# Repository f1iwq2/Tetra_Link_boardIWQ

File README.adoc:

Tetra_Link_boardIWQ
===================
 
Tetra board for the Pi Svxlink-tetra
Kicad Electronic Schematics & documentation
 
Carte Tetra pour le Pi
Schémas Kicad & documentation
 
image::interface_MTM800E_V4.jpg[]

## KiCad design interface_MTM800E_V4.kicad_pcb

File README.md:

# Tetra Link board
Tetra board for the Pi Svxlink-tetra
 Kicad Electronic Schematics & documentation
 
 (dir doc)
Carte Svxlink Tetra pour le Pi
 Schémas Kicad & documentation
 (rep doc)

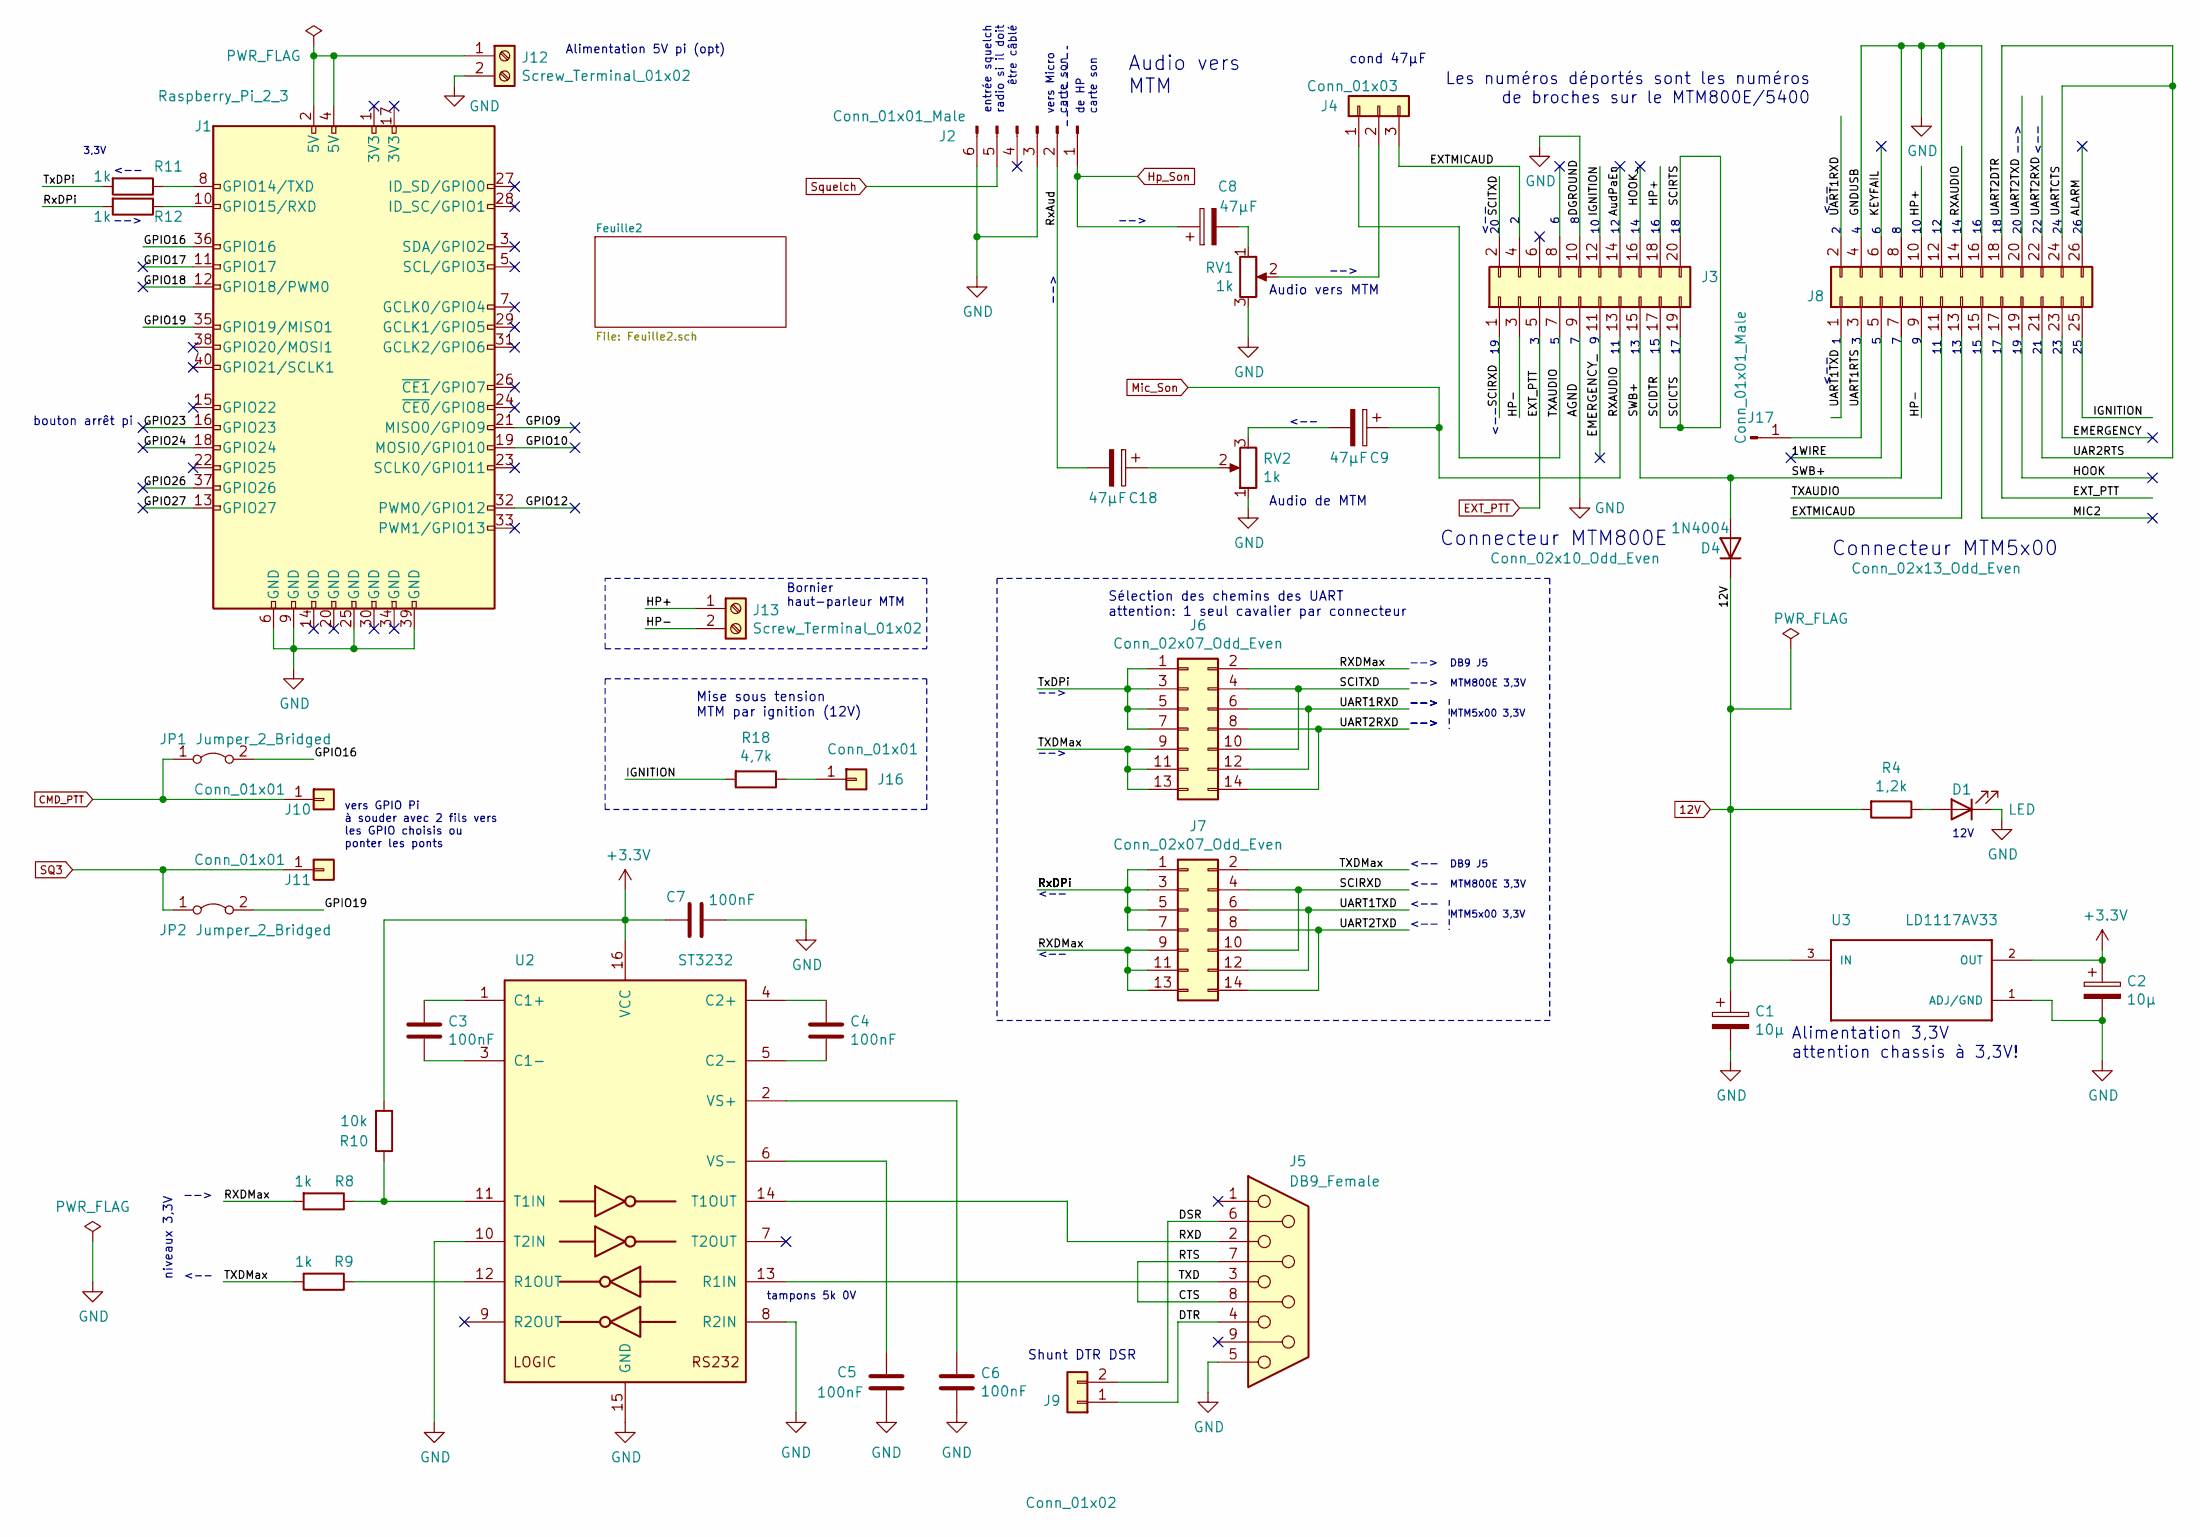
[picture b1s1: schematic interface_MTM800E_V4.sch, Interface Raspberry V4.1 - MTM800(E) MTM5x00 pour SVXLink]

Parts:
C1, C2: 10µ; CP_Radial_D5.0mm_P2.50mm
C3, C4, C5, C6, C7: 100nF; C_0805_2012Metric
C8, C9, C18: 47µF; CP_Radial_D4.0mm_P2.00mm
D1: LED; LED_D3.0mm
D4: 1N4004; D_A-405_P5.08mm_Vertical_AnodeUp
J1: Raspberry_Pi_2_3; raspberrypi2
J2: Conn_01x01_Male; PinHeader_1x06_P2.54mm_Vertical
J3: Conn_02x10_Odd_Even; PinHeader_2x10_P2.54mm_Vertical
J4: Conn_01x03; PinHeader_1x03_P2.54mm_Vertical
J5: DB9_Female; DSUB-9_Female_Horizontal_P2.77x2.84mm_EdgePinOffset9.90mm_H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
J6, J7: Conn_02x07_Odd_Even; PinHeader_2x07_P2.54mm_Vertical
J8: Conn_02x13_Odd_Even; PinHeader_2x13_P2.54mm_Vertical
J9: Conn_01x02; PinHeader_1x02_P2.54mm_Vertical
J10, J11: Conn_01x01; TestPoint_Loop_D2.50mm_Drill1.0mm
J12, J13: Screw_Terminal_01x02; TerminalBlock_bornier-2_P5.08mm
J16: Conn_01x01; PinHeader_1x01_P2.54mm_Vertical
J17: Conn_01x01_Male; PinHeader_1x01_P2.54mm_Vertical
JP1, JP2: Jumper_2_Bridged; SolderJumper-2_P1.3mm_Open_TrianglePad1.0x1.5mm
R4: 1,2k; R_Axial_DIN0207_L6.3mm_D2.5mm_P7.62mm_Horizontal
R8: 1k; R_Axial_DIN0207_L6.3mm_D2.5mm_P7.62mm_Horizontal
R9, R11, R12: 1k; R_Axial_DIN0204_L3.6mm_D1.6mm_P2.54mm_Vertical
R10: 10k; R_Axial_DIN0207_L6.3mm_D2.5mm_P7.62mm_Horizontal
R18: 4,7k; R_Axial_DIN0207_L6.3mm_D2.5mm_P7.62mm_Horizontal
RV1, RV2: 1k; Potentiometer_Bourns_3296W_Vertical
U2: ST3232; SOIC-16_3.9x9.9mm_P1.27mm
U3: LD1117AV33; TO255P1020X450X1968-3

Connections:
12V: C1.1, D4.1 (K), R4.2, U3.3 (IN); also elsewhere on the board
+3V3: C2.1, C7.1, R10.2, U2.16 (VCC), U3.2 (OUT); also elsewhere on the board
/1WIRE: J8.5
/ALARM: J8.26
/AudPaEn: J3.14
/CTS: J5.7, J5.8
/DSR: J5.6, J9.2
/DTR: J5.4, J9.1
/EMERGENCY: J8.23
/EMERGENCY_: J3.11
/EXTMICAUD: J3.4, J4.3, J8.13
/GPIO9: J1.21 (MISO0/GPIO9)
/GPIO10: J1.19 (MOSI0/GPIO10)
/GPIO12: J1.32 (PWM0/GPIO12)
/GPIO16: J1.36 (GPIO16), JP1.2 (B)
/GPIO17: J1.11 (GPIO17)
/GPIO18: J1.12 (GPIO18/PWM0)
/GPIO19: J1.35 (GPIO19/MISO1), JP2.2 (B)
/GPIO23: J1.16 (GPIO23)
/GPIO24: J1.18 (GPIO24)
/GPIO26: J1.37 (GPIO26)
/GPIO27: J1.13 (GPIO27)
/HOOK: J8.19
/HOOK_: J3.16
/HP+: J3.18, J8.10, J13.1
/HP-: J3.3, J8.9, J13.2
/IGNITION: J3.12, J8.25, R18.2
/KEYFAIL: J8.6
/MIC2: J8.15
/RXD: J5.2, U2.14 (T1OUT)
/RXDMax: J6.2, J7.9, J7.11, J7.13, R8.2
/RxDPi: J7.1, J7.3, J7.5, J7.7, R12.2
/SCICTS: J3.17, J3.19, J3.20
/SCIRXD: J3.1, J7.4, J7.10
/SCITXD: J3.2, J6.4, J6.10
/SWB+: D4.2 (A), J3.15, J8.7
/TXAUDIO: J3.7, J4.1, J8.11
/TXD: J5.3, U2.13 (R1IN)
/TXDMax: J6.9, J6.11, J6.13, J7.2, R9.2
/TxDPi: J6.1, J6.3, J6.5, J6.7, R11.2
/UAR2RTS: J8.18, J8.21, J8.24
/UART1RTS: J8.3, J17.1
/UART1RXD: J6.6, J6.12, J8.2
/UART1TXD: J7.6, J7.12, J8.1
/UART2RXD: J6.8, J6.14, J8.22
/UART2TXD: J7.8, J7.14, J8.20
CMD_PTT: J10.1, JP1.1 (A); also elsewhere on the board
EXT_PTT: J3.5, J8.17; also elsewhere on the board
GND: C1.2, C2.2, C5.2, C6.2, C7.2, D1.1 (K), J1.6 (GND), J1.9 (GND), J1.25 (GND), J1.39 (GND), J2.3, J2.6, J3.9, J3.10, J5.5, J8.4, J8.8, J8.12, J8.16, J12.2, RV1.3, RV2.1, U2.8 (R2IN), U2.10 (T2IN), U2.15 (GND), U3.1 (ADJ/GND); also elsewhere on the board
Mic_Son: C9.1, J3.13, J8.14; also elsewhere on the board
unnamed: C3.1, U2.1 (C1+)
unnamed: C3.2, U2.3 (C1-)
unnamed: C4.1, U2.4 (C2+)
unnamed: C4.2, U2.5 (C2-)
unnamed: C5.1, U2.6 (VS-)
unnamed: C6.1, U2.2 (VS+)
unnamed: C9.2, RV2.3
unnamed: D1.2 (A), R4.1
unnamed: J1.2 (5V), J1.4 (5V), J12.1
unnamed: J1.8 (GPIO14/TXD), R11.1
unnamed: J1.10 (GPIO15/RXD), R12.1
unnamed: J4.2, RV1.2
unnamed: J16.1, R18.1
unnamed: R9.1, U2.12 (R1OUT)
unnamed: R8.1, R10.1, U2.11 (T1IN)
SQ3: J11.1, JP2.1 (A); also elsewhere on the board
Squelch: J2.5; also elsewhere on the board

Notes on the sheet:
Connecteur MTM800E
Les numéros déportés sont les numéros de broches sur le MTM800E/5400
Audio vers MTM
Audio de MTM
niveaux 3,3V
Alimentation 3,3V attention chassis à 3,3V!
Connecteur MTM5x00
Shunt DTR DSR
vers GPIO Pi à souder avec 2 fils vers les GPIO choisis ou ponter les ponts
Alimentation 5V pi (opt)
vers Micro carte son
de HP carte son
12V
Bornier haut-parleur MTM
<--
-->
tampons 5k 0V
bouton arrêt pi
Mise sous tension MTM par ignition (12V)
Sélection des chemins des UART attention: 1 seul cavalier par connecteur
Audio vers MTM
entrée squelch radio si il doit être câblé
MTM800E 3,3V
MTM5x00 3,3V
3,3V
DB9 J5
cond 47µF

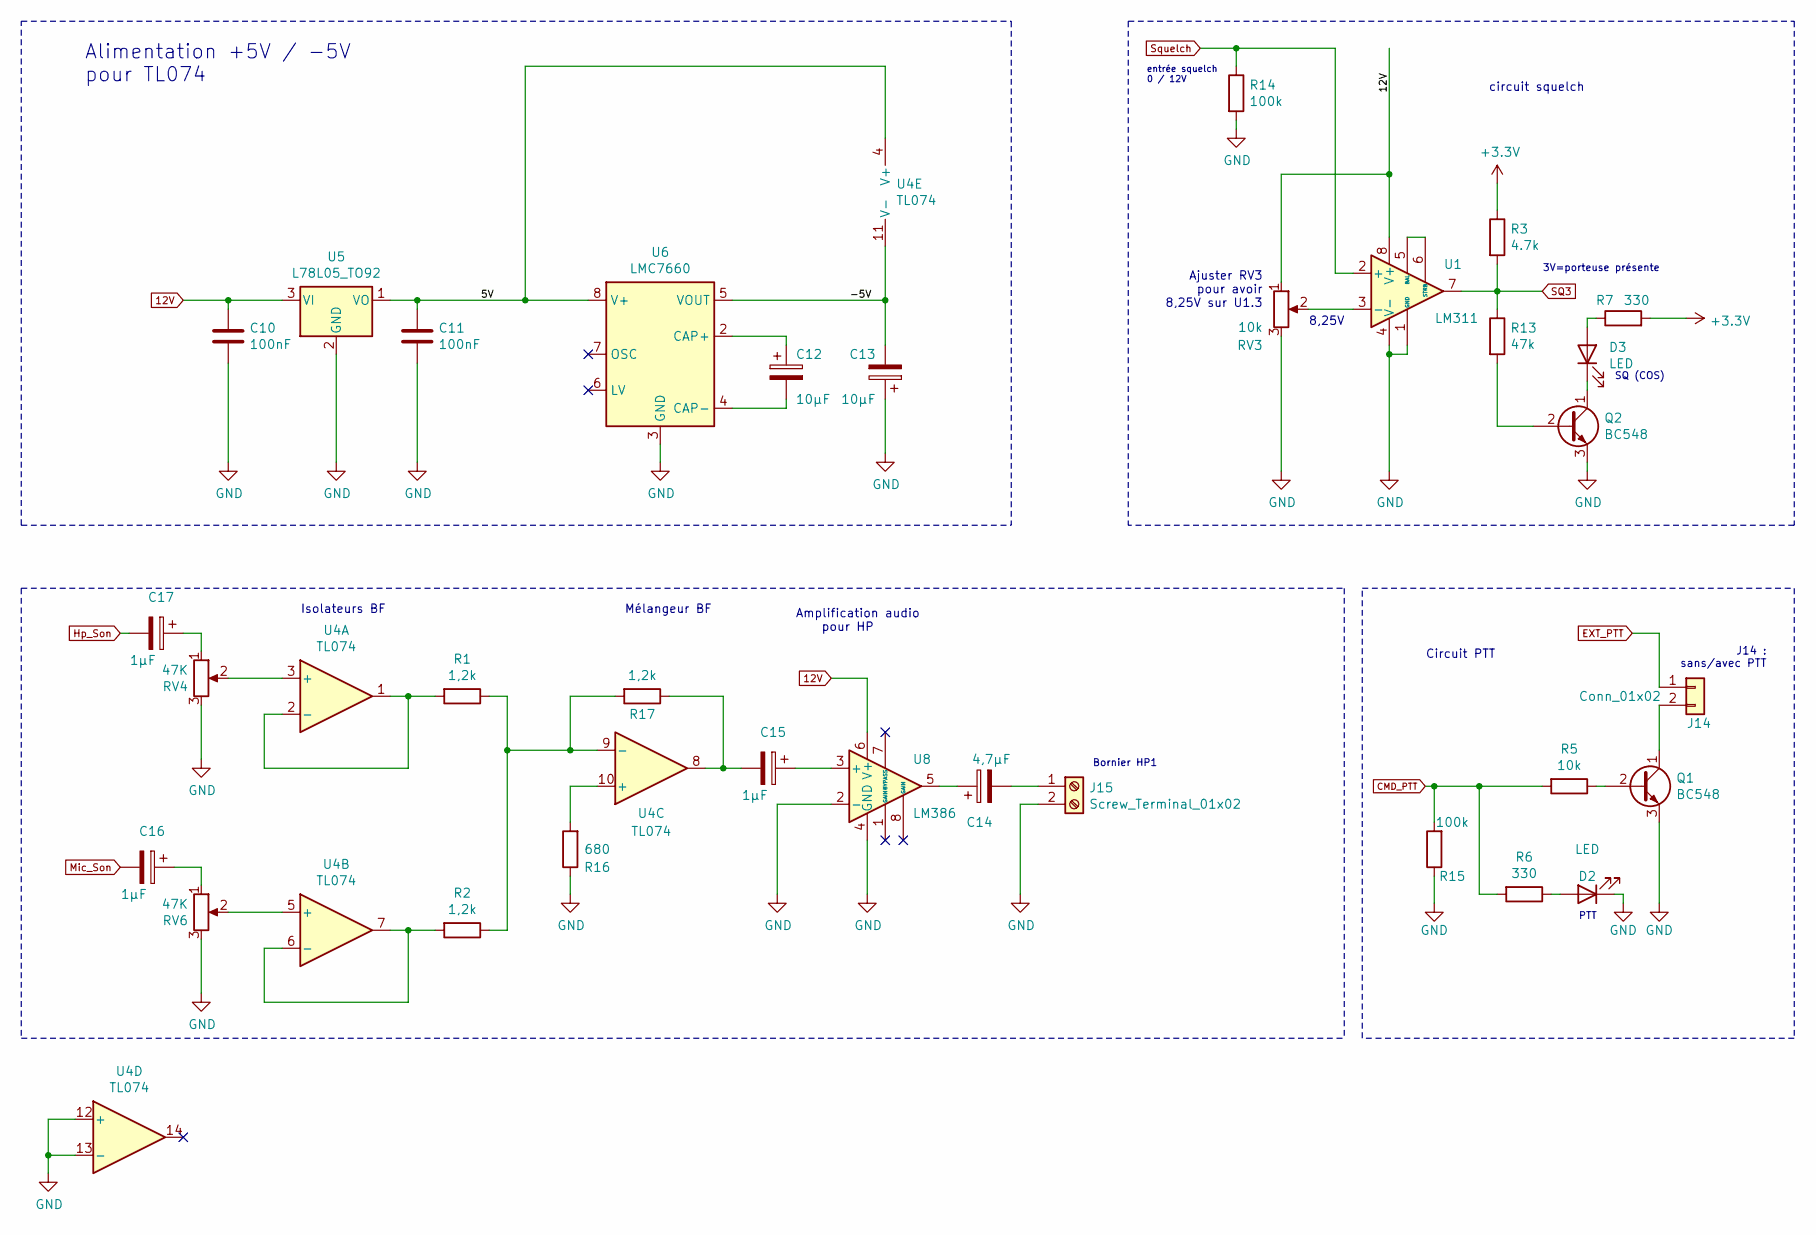
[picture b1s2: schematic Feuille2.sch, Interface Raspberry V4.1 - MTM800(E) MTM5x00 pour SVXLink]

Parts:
C10, C11: 100nF; C_Rect_L7.0mm_W2.5mm_P5.00mm
C12, C13: 10µF; CP_Radial_D4.0mm_P2.00mm
C14: 4,7µF; CP_Radial_D4.0mm_P2.00mm
C15, C16, C17: 1µF; CP_Radial_D4.0mm_P2.00mm
D2, D3: LED; LED_D3.0mm
J14: Conn_01x02; PinHeader_1x02_P2.54mm_Vertical
J15: Screw_Terminal_01x02; TerminalBlock_bornier-2_P5.08mm
Q1, Q2: BC548; TO-92_Inline_Wide
R1, R2, R17: 1,2k; R_Axial_DIN0207_L6.3mm_D2.5mm_P7.62mm_Horizontal
R3: 4.7k; R_Axial_DIN0207_L6.3mm_D2.5mm_P7.62mm_Horizontal
R5: 10k; R_Axial_DIN0207_L6.3mm_D2.5mm_P7.62mm_Horizontal
R6, R7: 330; R_Axial_DIN0207_L6.3mm_D2.5mm_P7.62mm_Horizontal
R13: 47k; R_Axial_DIN0207_L6.3mm_D2.5mm_P7.62mm_Horizontal
R14: 100k; R_Axial_DIN0204_L3.6mm_D1.6mm_P2.54mm_Vertical
R15: 100k; R_Axial_DIN0207_L6.3mm_D2.5mm_P7.62mm_Horizontal
R16: 680; R_Axial_DIN0207_L6.3mm_D2.5mm_P7.62mm_Horizontal
RV3: 10k; Potentiometer_Bourns_3296W_Vertical
RV4, RV6: 47K; Potentiometer_Bourns_3296W_Vertical
U1: LM311; DIP-8_W7.62mm_LongPads
U4: TL074; SOIC-14_3.9x8.7mm_P1.27mm
U5: L78L05_TO92; TO-92L_Inline_Wide
U6: LMC7660; SOIC-8_3.9x4.9mm_P1.27mm
U8: LM386; DIP-8_W7.62mm_LongPads

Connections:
12V: C10.1, RV3.1, U1.8 (V+), U5.3 (VI), U8.6 (V+); also elsewhere on the board
+3V3: R3.1, R7.2; also elsewhere on the board
/Feuille2/5V: C11.1, U4.4 (V+), U5.1 (VO), U6.8 (V+)
/Feuille2/-5V: C13.2, U4.11 (V-), U6.5 (VOUT)
CMD_PTT: R5.2, R6.2, R15.2; also elsewhere on the board
EXT_PTT: J14.1; also elsewhere on the board
GND: C10.2, C11.2, C13.1, D2.1 (K), J15.2, Q1.3 (E), Q2.3 (E), R14.2, R15.1, R16.1, RV3.3, RV4.3, RV6.3, U1.1 (GND), U1.4 (V-), U4.12 (+), U4.13 (-), U5.2 (GND), U6.3 (GND), U8.2 (-), U8.4 (GND); also elsewhere on the board
Mic_Son: C16.2; also elsewhere on the board
unnamed: C12.1, U6.2 (CAP+)
unnamed: C12.2, U6.4 (CAP-)
unnamed: C14.1, U8.5
unnamed: C14.2, J15.1
unnamed: C15.1, U8.3 (+)
unnamed: C15.2, R17.1, U4.8
unnamed: C16.1, RV6.1
unnamed: C17.1, RV4.1
unnamed: D2.2 (A), R6.1
unnamed: D3.1 (K), Q2.1 (C)
unnamed: D3.2 (A), R7.1
unnamed: J14.2, Q1.1 (C)
unnamed: Q1.2 (B), R5.1
unnamed: Q2.2 (B), R13.2
unnamed: R1.1, R2.1, R17.2, U4.9 (-)
unnamed: R1.2, U4.1, U4.2 (-)
unnamed: R2.2, U4.6 (-), U4.7
unnamed: R16.2, U4.10 (+)
unnamed: RV3.2, U1.3 (-)
unnamed: RV4.2, U4.3 (+)
unnamed: RV6.2, U4.5 (+)
unnamed: U1.5 (BAL), U1.6 (STRB)
SQ3: R3.2, R13.1, U1.7; also elsewhere on the board
Squelch: R14.1, U1.2 (+); also elsewhere on the board

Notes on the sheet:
Alimentation +5V / -5V pour TL074
Amplification audio pour HP
Bornier HP1
Mélangeur BF
Isolateurs BF
8,25V
3V=porteuse présente
SQ (COS)
Ajuster RV3 pour avoir 8,25V sur U1.3
circuit squelch
PTT
J14 : sans/avec PTT
Circuit PTT
entrée squelch 0 / 12V

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
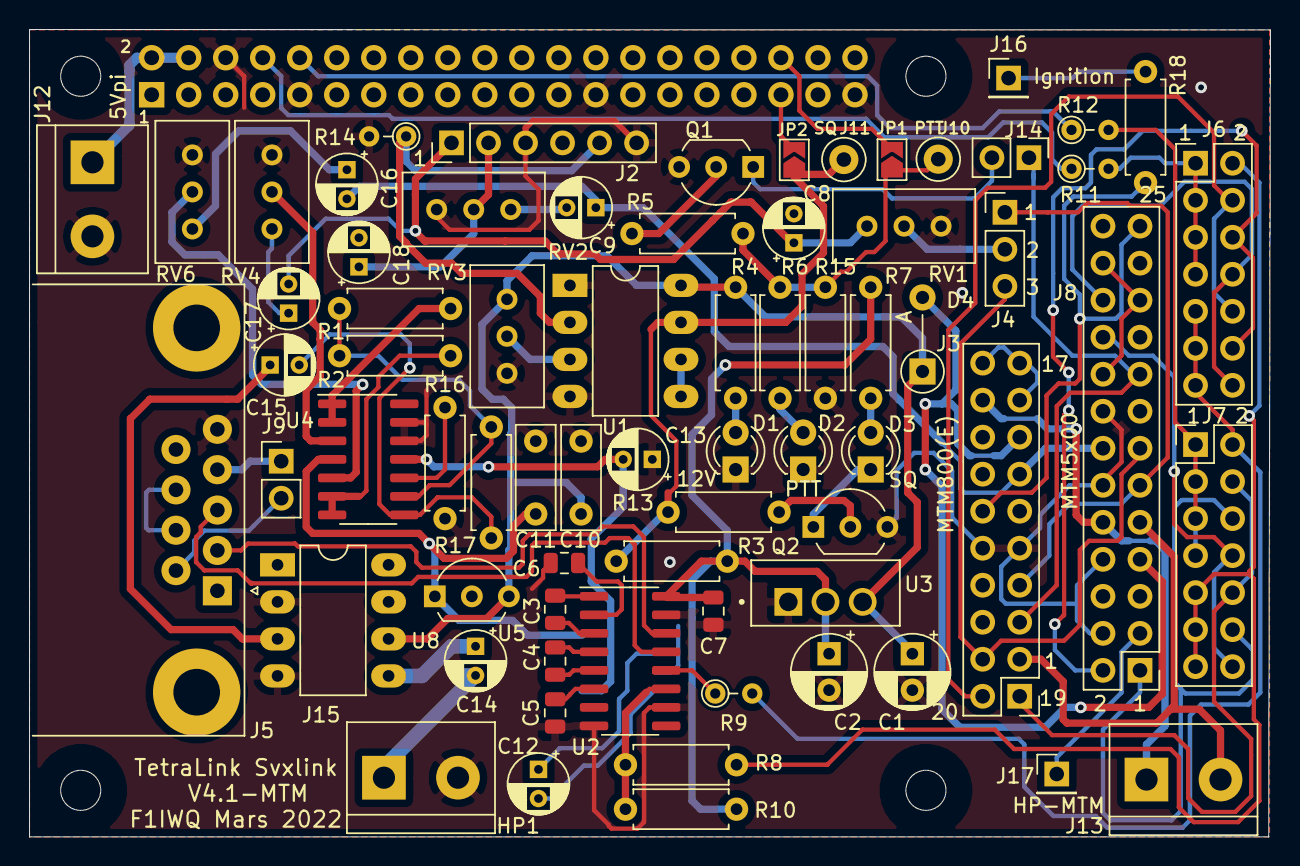
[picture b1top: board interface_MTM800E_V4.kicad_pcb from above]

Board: 2 copper layers, 85.2 x 55.4 mm, 73 parts (1 on the bottom side), 75 nets.

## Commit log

2021-03-20 V4.0
    V4.0
2021-03-21 V4.0-a
2022-04-07 V4.1
2022-04-17 upd2
2022-11-04 doc update
2025-04-04 update install docs for Raspbian >2024
2025-04-04 update 3
